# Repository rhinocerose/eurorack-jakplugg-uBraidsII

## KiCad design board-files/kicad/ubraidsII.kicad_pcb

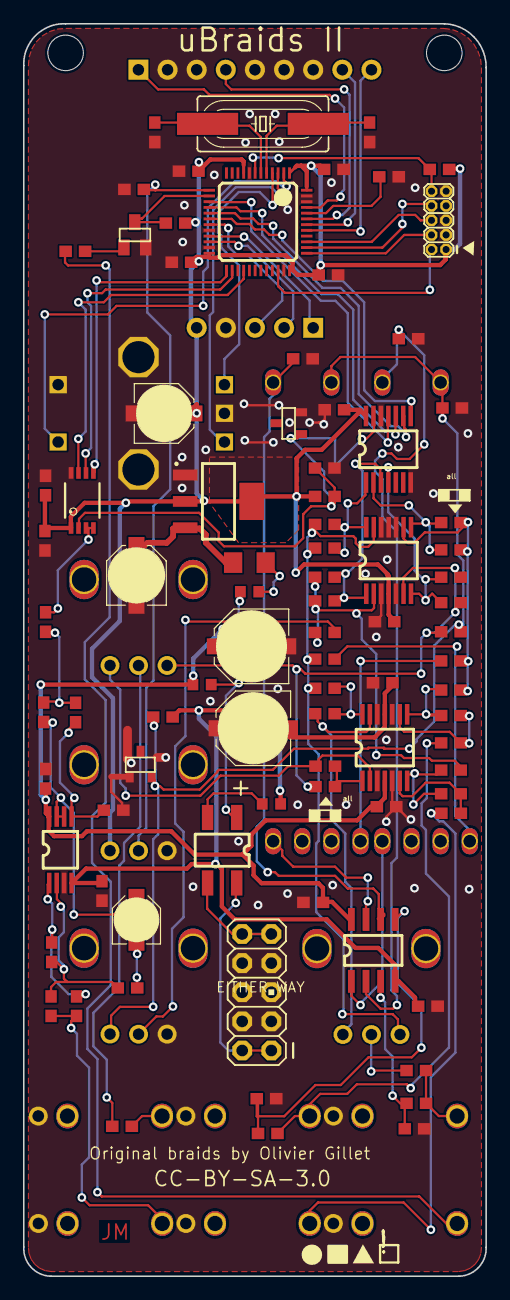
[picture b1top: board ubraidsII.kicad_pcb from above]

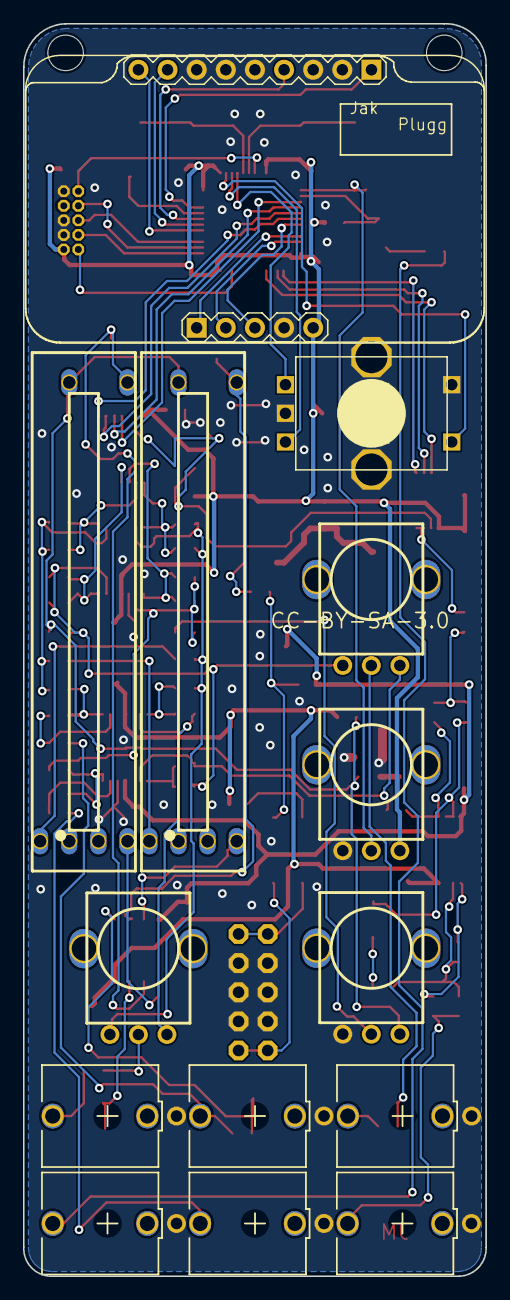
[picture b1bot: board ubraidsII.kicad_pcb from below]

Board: 2 copper layers, 40.3 x 109.2 mm, 103 parts (14 on the bottom side), 80 nets.

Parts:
@HOLE0, @HOLE1: (no value)
A1: DISPLAY-MODULE
C1: 100n; CAP_0603
C2: 100n; CAP_0603_C2
C3: 100n; CAP_0603_C3
C4: 100n; CAP_0603_C4
C5: 100n; CAP_0603_C5
C6: 1u; CAP_0603_C6
C7: 100n; CAP_0603_C7
C8: 470n; CAP_0603_C8
C9: 18p; CAP_0603_C9
C10: 18p; CAP_0603_C10
C11: 100n; CAP_0603_C11
C12: 1u; CAP_0603_C12
C13: 1n; CAP_0603_C13
C14: 1n; CAP_0603_C14
C15: 22u; PANASONIC_C
C16: 1n; CAP_0603_C16
C17: 1n; CAP_0603_C17
C18: 100n; CAP_0603_C18
C19: 22u; PANASONIC_C_C19
C20: 100n; CAP_0603_C20
C21: 100p; CAP_0603_C21
C22: 100p; CAP_0603_C22
C23: 100n; CAP_0603_C23
C24: 10u; PANASONIC_B
C25: 47u; PANASONIC_D
C26: 100n; CAP_0603_C26
C27: 100n; CAP_0603_C27
C28: 100n; CAP_0603_C28
C29: 47p; CAP_0603_C29
C30: 47u; PANASONIC_D_C30
C31: 100n; CAP_0603_C31
D3: SOP-4_6.5x2.54
IC3: LM4040B25; DBZ_R-PDSO-G3
IC4: MCP3204; TSSOP-14
IC5: DAC8551; MSOP-8
IC6: LM1117-3.3; SOT223-4
IC7: MCP6004; TSSOP-14_IC7
IC8: LM4040B10; DBZ_R-PDSO-G3_IC8
IC9: TL074D; TSSOP-14_IC9
IC10: TL072; TSSOP-8
J1: fm; Thonkiconn_Jack
J3: v oct; Thonkiconn_Jack_J3
J5: para 1; Thonkiconn_Jack_J5
J6: output; Thonkiconn_Jack_J6
J9: gate; Thonkiconn_Jack_J9
J10: para 2; Thonkiconn_Jack_J10
JP1: M05X2PTH; AVR_ICSP
JP2: M05X2MINIJTAG; 2X5-1.27
L1: IND_0603
L2: IND_0603_L2
L4: IND_0603_L4
Q5: 8MHz; HC49UP
Q6: MMBT3904; SOT23-BEC
R1: 1.2k; RES_0603
R2: 1.0M; RES_0603_R2
R3: 1.0M; RES_0603_R3
R4: 1.2k; RES_0603_R4
R5: 1.0M; RES_0603_R5
R6: 1.0M; RES_0603_R6
R19: 10kB; 9mm_Alpha_Bourns_Pot
R20: 10kB; 9mm_Alpha_Bourns_Pot_R20
R21: 10kB; 9mm_Alpha_Bourns_Pot_R21
R22: 10k; RES_0603_R22
R23: 1.0k; RES_0603_R23
R24: 100k; RES_0603_R24
R25: 49.9k; RES_0603_R25
R26: 49.9k; RES_0603_R26
R27: 10k; RES_0603_R27
R28: 200k; RES_0603_R28
R29: 100k; RES_0603_R29
R30: 24.9k; RES_0603_R30
R31: 24.9k; RES_0603_R31
R32: 200k; RES_0603_R32
R33: 10k; RES_0603_R33
R34: 24.9k; RES_0603_R34
R35: 24.9k; RES_0603_R35
R37: 10kB; 9mm_Alpha_Bourns_Pot_R37
R39: 120k; RES_0603_R39
R40: 200k; RES_0603_R40
R41: 24.9k; RES_0603_R41
R42: 24.9k; RES_0603_R42
R43: 24.9k; RES_0603_R43
R44: 24.9k; RES_0603_R44
R45: 39k; RES_0603_R45
R46: 39k; RES_0603_R46
R47: 100k; RES_0603_R47
R48: 100k; RES_0603_R48
R49: 4.7; R1206
R50: 24.9k; RES_0603_R50
R51: 330; RES_0603_R51
R52: 24.9k; RES_0603_R52
R53: 24.9k; RES_0603_R53
R54: 100k; RES_0603_R54
R55: 1.0k; RES_0603_R55
R56: 100k; RES_0603_R56
SW1: EC12E_SW; ALPS_EC12E_SW
U6: SOIC-8_150mil
UC1: STM32F103CBT6; LQFP48
VR1: para 1; BOURNS_PTL_30mm
VR2: 10k; BOURNS_PTL_30mm_VR2

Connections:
+3V3: A1.5, C2.1, C4.1, C5.1, C6.1, C7.1, C11.1, C12.1, C15.+, C18.1, IC4.14, IC5.1, IC6.2, IC6.4, IC7.4, JP2.1, R19.3, R22.2, R23.1, R27.2, UC1.1, UC1.9, UC1.24, UC1.36, UC1.48
ADC_MISO: IC4.10, UC1.16
ADC_MOSI: IC4.9, UC1.17
ADC_SCK: IC4.11, UC1.15
ADC_SS: IC4.8, UC1.18
AREF: C8.1, IC3.1, IC4.13, IC5.2, R23.2
AREF_-10: C26.1, IC8.2, R20.3, R40.1, R51.2, VR1.3, VR2.3
AUDIO_OUT: IC5.3, IC5.4, R45.2
BOOT_FLASH: R33.2, UC1.44
DAC_MOSI: IC5.7, UC1.28
DAC_SCK: IC5.6, UC1.26
DAC_SS: IC5.5, UC1.25
DISP_CHAR0: A1.9, UC1.43
DISP_CHAR1: A1.6, UC1.45
DISP_CHAR2: A1.14, UC1.41
DISP_CHAR3: A1.13, UC1.42
DISP_EN: A1.1, UC1.21
DISP_SCK: A1.2, UC1.22
DISP_SER: A1.3, UC1.19
ENC_A: SW1.B, UC1.3
ENC_B: SW1.A, UC1.4
ENC_CLICK: SW1.E, UC1.2
FINE_TUNE: C31.1, R19.2, UC1.13
FM_CV: C17.2, IC4.4, IC7.7, R35.2
GATE: Q6.C, R27.1, UC1.14
GND: A1.4, A1.7, A1.8, A1.10, A1.11, A1.12, C1.2, C2.2, C3.1, C4.2, C5.2, C6.2, C7.2, C8.2, C9.1, C10.1, C11.2, C12.2, C15.-, C18.2, C19.-, C20.1, C22.2, C23.2, C25.-, C26.2, C27.1, C28.2, C30.+, C31.2, IC3.2, IC4.7, IC4.12, IC5.8, IC6.1, IC7.3, IC7.5, IC7.10, IC7.11, IC7.12, IC8.1, IC9.3, IC9.5, IC9.10, IC9.12, IC10.3, J1.3, J3.3, J5.3, J6.3, J9.3, J10.3, JP1.3, JP1.4, JP1.5, JP1.6, JP1.7, JP1.8, JP2.3, JP2.5, JP2.9, Q6.E, R1.2, R2.1, R4.2, R5.1, R19.1, R19.4, R19.5, R20.1, R20.4, R20.5, R21.4, R21.5, R33.1, R37.4, R37.5, SW1.C, SW1.D, SW1.GND1, SW1.GND2, UC1.8, UC1.20, UC1.23, UC1.35, UC1.46, UC1.47, VR1.1, VR2.1
JTCK: JP2.4, UC1.37
JTDI: JP2.8, UC1.38
JTDO: JP2.6, UC1.39
JTMS: JP2.2, UC1.34
unnamed: R2.2, R3.2, U6.3
unnamed: C9.2, Q5.2, UC1.5
unnamed: C10.2, Q5.1, UC1.6
unnamed: IC9.7, R41.1, R53.2
unnamed: R20.2, R39.1
unnamed: R1.1, U6.2, VR1.5
unnamed: C16.1, IC7.2, R34.1, R39.2, R41.2
unnamed: IC9.6, R53.1, R54.2
unnamed: R21.2, R24.2
unnamed: C19.+, IC6.3, R49.1
unnamed: IC9.13, R37.3, R43.1
unnamed: IC9.14, R30.1, R43.2
unnamed: IC9.2, R21.3, R52.1
unnamed: IC9.1, R42.1, R52.2
unnamed: C17.1, IC7.6, R21.1, R35.1, R40.2, R42.2
unnamed: D3.4, JP1.1, JP1.2
unnamed: IC9.8, R31.1, R44.2
unnamed: C13.1, IC7.13, R25.1, R28.2, R30.2, R37.1
unnamed: R28.1, VR1.2
unnamed: R37.2, R48.2
unnamed: IC9.9, R44.1, R47.2
unnamed: D3.3, JP1.9, JP1.10
unnamed: R32.1, VR2.2
unnamed: Q6.B, R29.2
unnamed: C21.2, C24.+, IC10.6, IC10.7
unnamed: C24.-, R50.2
unnamed: C22.1, IC10.5, R46.1
unnamed: C14.1, IC7.9, R26.1, R31.2, R32.2
unnamed: C21.1, R45.1, R46.2
unnamed: J6.2, R55.1, R56.1
unnamed: C29.2, IC10.1, R55.2
unnamed: C29.1, IC10.2, R50.1, R56.2
Net_0: J9.2, R29.1
Net_1: J3.2, R54.1
Net_2: J5.2, R3.1, R48.1
Net_3: U6.7, VR2.6
Net_12: U6.1, VR1.6
Net_42: J1.2, R24.1
Net_55: J10.2, R6.1, R47.1
Net_80: R4.1, U6.6, VR2.5
Net_81: R5.2, R6.2, U6.5
Net_106: D3.1, L2.2, L4.1
Net_107: D3.2, L1.2
Net_110: L4.2, R49.2
PARAM1_CV: C13.2, IC4.1, IC7.14, R25.2
PARAM2_CV: C14.2, IC4.2, IC7.8, R26.2
PITCH_CV: C16.2, IC4.3, IC7.1, R34.2
RESET: JP2.10, R22.1, UC1.7
VCC: C3.2, C23.1, C25.+, C28.1, IC9.4, IC10.8, L2.1, U6.8
VEE: C1.1, C20.2, C27.2, C30.-, IC9.11, IC10.4, L1.1, R51.1, U6.4

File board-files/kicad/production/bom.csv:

Designator,Footprint,Quantity,Value,LCSC Part #
"@HOLE0, @HOLE1",,2,,
A1,DISPLAY-MODULE,1,DISPLAY-MODULE,
C1,CAP_0603,1,100n,
C10,CAP_0603_C10,1,18p,
C11,CAP_0603_C11,1,100n,
C12,CAP_0603_C12,1,1u,
C13,CAP_0603_C13,1,1n,
C14,CAP_0603_C14,1,1n,
C15,PANASONIC_C,1,22u,
C16,CAP_0603_C16,1,1n,
C17,CAP_0603_C17,1,1n,
C18,CAP_0603_C18,1,100n,
C19,PANASONIC_C_C19,1,22u,
C2,CAP_0603_C2,1,100n,
C20,CAP_0603_C20,1,100n,
C21,CAP_0603_C21,1,100p,
C22,CAP_0603_C22,1,100p,
C23,CAP_0603_C23,1,100n,
C24,PANASONIC_B,1,10u,
C25,PANASONIC_D,1,47u,
C26,CAP_0603_C26,1,100n,
C27,CAP_0603_C27,1,100n,
C28,CAP_0603_C28,1,100n,
C29,CAP_0603_C29,1,47p,
C3,CAP_0603_C3,1,100n,
C30,PANASONIC_D_C30,1,47u,
C31,CAP_0603_C31,1,100n,
C4,CAP_0603_C4,1,100n,
C5,CAP_0603_C5,1,100n,
C6,CAP_0603_C6,1,1u,
C7,CAP_0603_C7,1,100n,
C8,CAP_0603_C8,1,470n,
C9,CAP_0603_C9,1,18p,
D3,SOP-4_6.5x2.54,1,,
IC10,TSSOP-8,1,TL072,
IC3,DBZ_R-PDSO-G3,1,LM4040B25,
IC4,TSSOP-14,1,MCP3204,
IC5,MSOP-8,1,DAC8551,
IC6,SOT223-4,1,LM1117-3.3,
IC7,TSSOP-14_IC7,1,MCP6004,
IC8,DBZ_R-PDSO-G3_IC8,1,LM4040B10,
IC9,TSSOP-14_IC9,1,TL074D,
J1,Thonkiconn_Jack,1,fm,
J10,Thonkiconn_Jack_J10,1,para 2,
J3,Thonkiconn_Jack_J3,1,v oct,
J5,Thonkiconn_Jack_J5,1,para 1,
J6,Thonkiconn_Jack_J6,1,output,
J9,Thonkiconn_Jack_J9,1,gate,
JP1,AVR_ICSP,1,M05X2PTH,
JP2,2X5-1.27,1,M05X2MINIJTAG,
L1,IND_0603,1,,
L2,IND_0603_L2,1,,
L4,IND_0603_L4,1,,
Q5,HC49UP,1,8MHz,
Q6,SOT23-BEC,1,MMBT3904,
R1,RES_0603,1,1.2k,
R19,9mm_Alpha_Bourns_Pot,1,10kB,
R2,RES_0603_R2,1,1.0M,
R20,9mm_Alpha_Bourns_Pot_R20,1,10kB,
R21,9mm_Alpha_Bourns_Pot_R21,1,10kB,
R22,RES_0603_R22,1,10k,
R23,RES_0603_R23,1,1.0k,
R24,RES_0603_R24,1,100k,
R25,RES_0603_R25,1,49.9k,
R26,RES_0603_R26,1,49.9k,
R27,RES_0603_R27,1,10k,
R28,RES_0603_R28,1,200k,
R29,RES_0603_R29,1,100k,
R3,RES_0603_R3,1,1.0M,
R30,RES_0603_R30,1,24.9k,
R31,RES_0603_R31,1,24.9k,
R32,RES_0603_R32,1,200k,
R33,RES_0603_R33,1,10k,
R34,RES_0603_R34,1,24.9k,
R35,RES_0603_R35,1,24.9k,
R37,9mm_Alpha_Bourns_Pot_R37,1,10kB,
R39,RES_0603_R39,1,120k,
R4,RES_0603_R4,1,1.2k,
R40,RES_0603_R40,1,200k,
R41,RES_0603_R41,1,24.9k,
R42,RES_0603_R42,1,24.9k,
R43,RES_0603_R43,1,24.9k,
R44,RES_0603_R44,1,24.9k,
R45,RES_0603_R45,1,39k,
R46,RES_0603_R46,1,39k,
R47,RES_0603_R47,1,100k,
R48,RES_0603_R48,1,100k,
R49,R1206,1,4.7,
R5,RES_0603_R5,1,1.0M,
R50,RES_0603_R50,1,24.9k,
R51,RES_0603_R51,1,330,
R52,RES_0603_R52,1,24.9k,
R53,RES_0603_R53,1,24.9k,
R54,RES_0603_R54,1,100k,
R55,RES_0603_R55,1,1.0k,
R56,RES_0603_R56,1,100k,
R6,RES_0603_R6,1,1.0M,
SW1,ALPS_EC12E_SW,1,EC12E_SW,
U6,SOIC-8_150mil,1,,
UC1,LQFP48,1,STM32F103CBT6,
VR1,BOURNS_PTL_30mm,1,para 1,
VR2,BOURNS_PTL_30mm_VR2,1,10k,

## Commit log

2025-08-07 Kicad
2025-08-14 Added BOM

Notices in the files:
board-files/kicad/ubraidsII.kicad_pcb:
CC-BY-SA-3.0
